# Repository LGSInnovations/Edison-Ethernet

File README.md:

Edison Ethernet Block
=====================

This project gives the Intel Edison ethernet capibility in applications where wired connections are necessary or more reliable.

Currently, there are two common Linux distros used on the Intel Edison: Yocto Linux and Ubilinux. The Edison Ethernet project has support for both and is created from forking those distros.

## Distro Support ##

We currently support a Debian based distro, based on Ubilinux, and the Yocto distro. Both are built with the Yocto 3.10 kernel, bitbaked with driver support for the LAN9512/SMSC95xx USB-to-Ethernet chip.

#### Ubilinux/Debian ####

Popular for its familiar package manager (`apt-get`), this build has support for the Edison Ethernet block as well as support for MAC spoofing using a tool called [macchanger](https://github.com/alobbs/macchanger).

#### Yocto ####

This Linux distro is great for lightweight projects as it has a rootfs size of about 500MB. Although it has support for the Edison Ethernet block, it does not currently have easy support for MAC spoofing through macchanger.

## Installation and Setup ##

To start using the Edison Ethernet block, there are four options, increasing in time/difficulty:

1. Download the binary release of the `smsc95xx.ko` driver and add it to your kernel modules.
2. Download pre-packaged images of this project ready to flash with the smsc95xx.ko module baked in.
3. Clone the Edison-Ethernet git project to avoid using bitbake, but still allowing you flexibility to add/remove files from the rootfs. Build the debian or yocto image and then flash using `./flashall.sh` such as illustrated at the end of the guide [here](https://github.com/LGSInnovations/Edison-Ethernet/blob/master/guides/customize-yocto-kernel.md)
4. Build from source using `bitbake` and `menuconfig` and flash your device using `./flashall.sh`.

#### Option 1 - Binary Release ####

Download the release corresponding to your board. Extract the files.

Inside the release, there is a directory called `modules`. You'll find different kernel versions inside. To know which kernel module to install on your Edison, run `uname -r` and pick the corresponding directory inside the release. If your kernel version is not available, create an issue and we will release one for that version. You can also make your own by following [these](guides/version-magic-error.md) instructions.

Once you know which kernel version to use, follow [these](guides/installation.md) instructions to copy and install on your Edison.

#### Option 2 - Pre-packed Images ####

Download the release corresponding to your board. Extract the files.

Inside the release, there is a directory called `images`. You'll find two tarballs: `yocto.tar.gz` and `debian.tar.gz`. Extract your choice of distro and use `sudo ./flashall.sh` as normal.

#### Option 3 - Leverage This Project ####

See *Contributing to this Project* below.

#### Option 4 - Build from Source ####

Follow [these](guides) instructions. *Be aware that this will take at least 5+ hours.*

## Contributing to this Project ##

We use Git Submodules in our repo, if you've never used that tool before, make sure to read about it [here](https://git-scm.com/book/en/v2/Git-Tools-Submodules).

#### Development Environment ####

All developent must be on a Linux machine. Because of the naming convention of files in the decompressed rootfs of Linux, Mac OS and Windows will groan about invalid file names. We use [Ubuntu 14.04.02](http://releases.ubuntu.com/14.04/) for our host environment.

#### Getting the Source ####

Source code / files can be cloned as follows:

```bash
git clone --recursive https://github.com/LGSInnovations/Edison-Ethernet.git # The '--recursive' flag will also clone the submodules 
```

#### Packaging Your Changes ####

After you have changed things to your liking, use the `package.sh` script in `Edison-Ethernet/src/` to package your `edison-image-edison.ext4` rootfs so you can run `sudo ./flashall.sh`. Make sure that you have pulled in the latest changes in the `edison-debain-image` and/or `edison-yocto-image` submodules.

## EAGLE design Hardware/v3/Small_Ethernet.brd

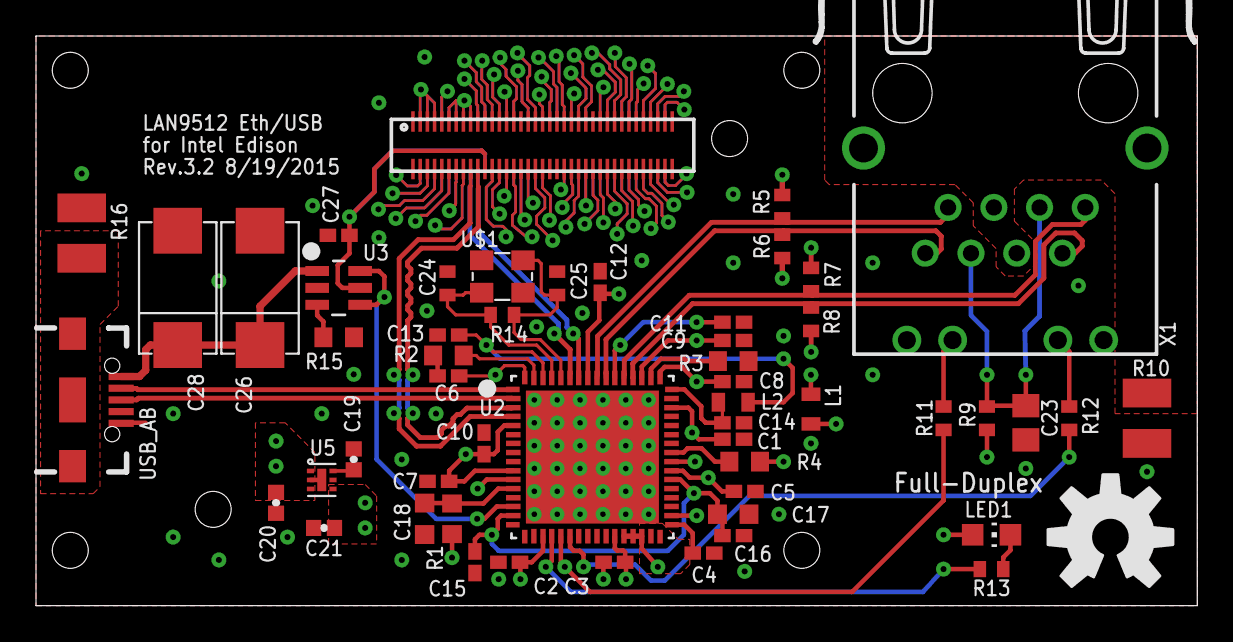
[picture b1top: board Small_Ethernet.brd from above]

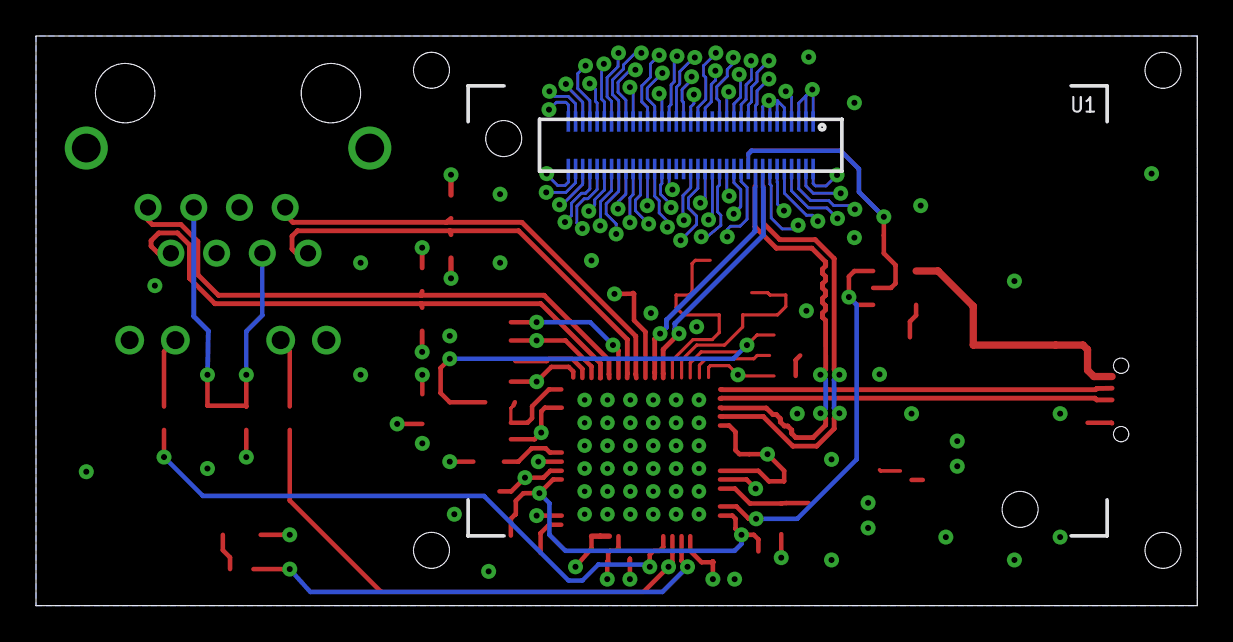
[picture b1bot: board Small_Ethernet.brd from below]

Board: 4 copper layers, 64.5 x 31.6 mm, 55 parts (2 on the bottom side), 90 nets.

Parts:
C1, C2, C3, C4, C5, C6, C7, C8, C9, C10, C11, C12, C14, C15, C16: 0.1; C0402K
C13, C27: 1.0; C0402K
C17: 4.7; C0603K
C18: 0.01uF; C0603K
C19: .1uF; 0402-CAP
C20, C21: 1uF; 0402-CAP
C23: 0.022uF; C0805
C24, C25: 33pF; C0402
C26, C28: CAP-2917
E$2: OSHW-LOGO-L
L1, L2: 2.0A 120Ohm; L0603
LED1: Green LED; CHIP-LED0805
R1, R4: 10K; R0603
R2: 12K; R0603
R3: 12.4K; R0603
R5, R6, R7, R8: 49.9; R0402
R9: 10; R0402
R10, R16: 0; R1210
R11, R12, R13: 330; R0402
R14: 1M; R0402
R15: 56k; R0603
U1: EDISON_CONNECTOR_FULLMOUNTING_HOLES; EDISON_DAUGHTER
U2: LAN9512-JZX; QFN50P900X900X100-65N
U3: MAX4995AAUT+; 21-0058I
U4: EDISON_CONNECTOR_FULLHEADER; DF40C-70DP-0.4(51)
U5: 6-UFDFN
U$1: SMDCRYSTAL_3.2X2.5
USB_AB: USB-AB-MICRO-SMD_V03
X1: J1011F01P; J1

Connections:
BYP: C19.1, U5.P6
DSUSB_N: U2.1, USB_AB.D-1
DSUSB_P: U2.2, USB_AB.D+1
GND: C1.2, C2.2, C3.2, C4.2, C5.2, C6.2, C7.2, C8.2, C9.2, C10.2, C11.2, C12.2, C13.2, C14.2, C15.2, C16.2, C17.2, C18.2, C19.2, C20.1, C21.2, C23.2, C24.2, C25.2, C26.NEG, C27.2, C28.NEG, R2.2, R3.2, R10.2, R15.1, R16.2, U1.1, U1.3, U1.5, U1.9, U1.11, U1.13, U1.15, U2.34, U3.2, U4.1, U4.3, U4.5, U4.9, U4.11, U4.13, U4.15, U5.GND, U5.P2, U$1.P2_GND, U$1.P4_GND, USB_AB.GND1
GP28_I2C_6_SDA: U1.47, U4.47
unnamed: C13.1, L2.1, U2.62
unnamed: C14.1, L2.2, U2.48
unnamed: C15.1, C16.1, C17.1, U2.15, U2.38
unnamed: R2.1, U2.63
unnamed: C18.1, R1.1, U2.12
unnamed: R3.1, U2.50
unnamed: R4.1, U2.41
unnamed: C23.1, R9.1, X1.3, X1.6
unnamed: R11.2, U2.21
unnamed: R11.1, X1.10
unnamed: R12.1, X1.11
unnamed: R12.2, U2.22
unnamed: LED1.C, R13.1
unnamed: R13.2, U2.20
unnamed: C24.1, R14.1, U2.61, U$1.P1_I/O
unnamed: C25.1, R14.2, U2.60, U$1.P3_O/I
unnamed: U2.14, U3.4, U3.6
unnamed: R15.2, U3.3
P7: U1.7, U4.7
P12: U1.12, U4.12
P14: U1.14, U4.14
P17: U1.17, U4.17
P19: U1.19, U4.19
P21: U1.21, U4.21
P22: U1.22, U4.22
P23: U1.23, U4.23
P24: U1.24, U4.24
P25: U1.25, U4.25
P26: U1.26, U4.26
P27: U1.27, U4.27
P28: U1.28, U4.28
P30: U1.30, U4.30
P31: U1.31, U4.31
P32: U1.32, U4.32
P33: U1.33, U4.33
P34: U1.34, U4.34
P35: U1.35, U4.35
P36: U1.36, U4.36
P37: U1.37, U4.37
P39: U1.39, U4.39
P41: U1.41, U4.41
P42: U1.42, U4.42
P43: U1.43, U4.43
P44: U1.44, U4.44
P45: U1.45, U4.45
P46: U1.46, U4.46
P48: U1.48, U4.48
P50: U1.50, U4.50
P51: U1.51, U4.51
P52: U1.52, U4.52
P53: U1.53, U4.53
P54: U1.54, U4.54
P55: U1.55, U4.55
P56: U1.56, U4.56
P57: U1.57, U4.57
P58: U1.58, U4.58
P59: U1.59, U4.59
P60: U1.60, U4.60
P61: U1.61, U4.61
P62: U1.62, U4.62
P63: U1.63, U4.63
P64: U1.64, U4.64
P65: U1.65, U4.65
P66: U1.66, U4.66
P67: U1.67, U4.67
P68: U1.68, U4.68
P69: U1.69, U4.69
P70: U1.70, U4.70
RX_N: R8.1, U2.52, X1.7
RX_P: R7.1, U2.53, X1.8
S$5: U1.10, U4.10
S$6: U1.8, U4.8
SHLD: R10.1, X1.4, X1.5, X1.M1, X1.M2
TX_N: R5.1, U2.56, X1.2
TX_P: R6.1, U2.55, X1.1
USBSHLD: R16.1, USB_AB.SHIELD1, USB_AB.SHIELD2, USB_AB.SHIELD3
USBUP_N: U1.18, U2.58
USBUP_P: U1.16, U2.59
USB_D_N: U2.3, U4.18
USB_D_P: U2.4, U4.16
USB_VBUS: C27.1, U1.20, U3.5, U4.20
VBUS_OUT: C26.POS, C28.POS, U3.1, USB_AB.VBUS1
VDD3IO: C1.1, C2.1, C3.1, C4.1, C5.1, C21.1, L1.1, LED1.A, R1.2, R4.2, U2.11, U2.19, U2.27, U2.28, U2.29, U2.30, U2.32, U2.33, U2.39, U2.40, U2.46, U5.P4, X1.9, X1.12
VDD33A: C6.1, C7.1, C8.1, C9.1, C10.1, C11.1, C12.1, L1.2, R5.2, R6.2, R7.2, R8.2, R9.2, U2.5, U2.10, U2.49, U2.51, U2.54, U2.57, U2.64
VSYS: C20.2, U1.2, U1.4, U1.6, U4.2, U4.4, U4.6, U5.P1, U5.P3

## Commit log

2015-05-28 Added sane .config for yocto kernel build with SMS95XX module. Added some firewall blocked packages.
2015-05-28 organized .config to yocto folder
2015-05-29 Create Preliminary BOM
    Added preliminary BOM
2015-05-29 Delete Preliminary BOM
    Oops, I wanted to upload the file not like this.
2015-05-29 Create Preliminary BOM
    I can't create a repo to put it in so I'll just put it here. I'll most likely delete this and add the actual word document when I figure out how.
2015-05-29 Update Preliminary BOM
    Added Hirose connectors to BOM
2015-06-01 added libsdl1.2-dev to env setup, added the option of just using 'make', made the README a markdown file
2015-06-02 added swig, a missing package for bitbake
2015-06-02 more markdown formatting
2015-06-02 added setting up the network interface for yocto
2015-06-02 typos
2015-06-02 Added first revision of schematic and board. Board is not yet routed.
2015-06-02 Changed LED from 0805 package to 0603 package
2015-06-02 Rolled back previous change
2015-06-02 Include kernel update instructions
2015-06-02 Added preliminary BOM to go with Board Revision 1
2015-06-02 Changed the Name of the schematics to better match the BoM
2015-06-02 Removed Old schematics
2015-06-02 initial commit of ext4 image files from ubilinux
2015-06-02 Yocto README changes
2015-06-03 added some useful packages to include in debian image
2015-06-03 added instructions on what to do with debian packages for Edison
2015-06-03 moved ubilinux to seperate repo
2015-06-03 Updated schematic and BOM to Rev. 2. Removed one USB port and changed power delivery circuitry to downstream USB.
2015-06-03 Updated schematic and BOM to Rev. 2: Removed one USB and changed power supply circuitry for downstream USB. Removed old documents.
2015-06-03 added info about using the Yocto kernel in Ubilinux
2015-06-03 README key glyph fix
2015-06-03 again
2015-06-04 Added intitial 4 layer board layout and made very minor changes to Schematic and BOM.
2015-06-04 fixes
2015-06-05 Updated layout with better design rules, to match 4PCB.com
2015-06-05 Finished first board layout Board_4layer_R2
2015-06-08 Added Datasheets for all relevant components.
2015-06-08 Updated board and schematic as per recommendations.
2015-06-08 Added PDF Schematic
2015-06-08 Removed olf board file, made some changes to new board file and schematic. BOM is till complete.
2015-06-09 Added Xtal datasheet
2015-06-09 Revised board.
2015-06-09 Updated BOM to reflect layout changes.
2015-06-09 Added "Reference" folder with board layout/schematic references.
2015-06-09 Added new reference material
2015-06-09 small readme touch ups
2015-06-11 Board ready for manufacturing: Added mounting hardware and verified trace impedances. Designed to Advanced Circuit's specifications and passes their checks at FreeDFM.com.
2015-06-11 Updated BOM with qty and urls
2015-06-11 Updated BOM
2015-06-11 Updated board to final version and added CAM files.
2015-06-11 added edison-debian-image submodule, added toFlash dir
2015-06-11 updated package.sh
2015-06-11 package edits
2015-06-11 yocto package fix
2015-06-11 moved edison-debian-image to src dir
2015-06-11 updated config_mac to fix mount bug
2015-06-11 readme and yocto update
2015-06-11 added commands to the debian_package section
2015-06-11 subdir update
2015-06-11 yocto build working
2015-06-11 added package.sh empty file; updated flashall.sh; updated gitignore
2015-06-11 added yocto image submodule
2015-06-11 added Yocto kernel to src folder
2015-06-11 chown'ed mnt dir
2015-06-12 distro info
2015-06-12 Fixed board inconsistencies, airwires, stubs, etc. Passes FreeDFM.com checks with no errors and warnings. Exported CAM files.
2015-06-12 Minor changes
2015-06-15 edited yocto submodule
2015-06-15 hello
2015-06-15 help
2015-06-15 updated debian image
2015-06-16 Updated Yocto submodule
2015-06-16 Fixing broken submodule reference.
2015-06-24 PoE and SD card added
2015-06-24 Changed PoE module to accomodate USB_VBUS, changed Rectifiers, added level shifter
2015-06-25 Tied DCIN to VSYS, added LED, cleaned up Bridge Rectifiers
2015-06-26 Added R for min load
2015-06-29 Added downstream USB through hirose, fixed some connections between top and bottom connectors
2015-07-10 Updated BOM to include R17 - a minor oversight in the original BOM
2015-07-10 fixed BOM issue with 56kOhm vs. 56 ohm resistor (R15)
2015-07-10 adding steps for installation/setup
2015-07-10 updating README and subtrees
2015-07-10 emphasis
2015-07-10 fixed relative link
2015-07-13 added installation and version-magic-error guides; renamed yocto/ -> guides/
2015-07-13 finished installation, split up README into separate guides
2015-07-13 fixed bullets
2015-07-13 added binary and image instructions
2015-07-14 Create hookup-guide.md
    I put the other one in the wrong directory. This one is correct.
2015-07-17 PoE Board completed. Added Micro USB to schematic and board
2015-07-17 Fixed part labels, fixed a couple acute angles
2015-07-17 Fixed some 45 degree angles
2015-07-20 Fixed some stuff from DRC
2015-07-20 Got rid of unrouted airwires
2015-07-20 Connected shield pins on Ethernet jack
2015-07-21 Moved U8 to top of board, moved LED1 from under the Edison, put C28 back on the bottom
2015-07-21 Minor changes in via placement
2015-07-24 Added smaller version of original board. Minor changes to PoE board
2015-07-24 Added library file. Everything Chleo made & some devices from Sparkfun's libraries
2015-08-06 Added ground fills. PoE: power planes around U7, diode for power through microB. Small: changed C26 to 2 caps, removed NP caps, removed test points, replaced crystal
2015-08-07 Ready for final review
2015-08-10 Updated library and BOM
2015-08-10 Made downstream USB traces the same length; minor changes to PoE board
2015-08-10 Fixed stub traces around Edison connector
2015-08-17 Added LDO for power off VSYS (to ensure enough current to LAN); Added datasheets for LDO and FTDI chip
2015-08-17 Added LDO for power off VSYS, fixed SD card
2015-08-18 Changed R20
2015-08-19 Aesthetic changes for Ryan

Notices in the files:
parts and their libraries:
SparkFun-Connectors: Licensing: Creative Commons ShareAlike 4.0 International - https://creativecommons.org/licenses/by-sa/4.0
